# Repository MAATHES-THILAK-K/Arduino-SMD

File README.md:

# Arduino-SMD

GrabCAD Link: [https://grabcad.com/library/arduino-smd-1](https://grabcad.com/library/arduino-smd-1)

This project is a compact, stylish, Arduino-compatible development board based on the **ATmega328P-AU** (TQFP). It includes several integrated peripherals making it ideal for wearable or IoT projects.

---

## 📦 Components

| Component                              | Description                               |
| -------------------------------------- | ----------------------------------------- |
| **ATmega328P-AU**                      | 8-bit microcontroller (TQFP)              |
| **AMS1117-3.3V LDO**                   | 5V to 3.3V regulator for APDS9960 & HC-05 |
| **TLV76750**                           | 12V to 5V LDO                             |
| **WS2812B**                            | RGB LED (Smart addressable)               |
| **APDS-9960**                          | Gesture sensor (I2C)                      |
| **HC-05**                              | Bluetooth module                          |
| **Tactile Switch**                     | User input                                |
| **Active Buzzer**                      | Sound feedback                            |
| **USB-C (Power-only)**                 | 5V input only (no data lines)             |
| **12V Barrel Jack**                    | Additional power input                    |
| **ICSP Header (2x3)**                  | For firmware flashing                     |
| **GPIO Headers**                       | Female headers for D0-D13, A0-A5          |
| **Various SMD Resistors & Capacitors** | For pull-ups, bypassing, filtering        |

---

## ⚠️ Warning

> **The DRC (Design Rule Check) in KiCad was not fully resolved during initial layout. There may be trace width, clearance, or connectivity issues. Please verify the layout manually or run a complete DRC pass before fabrication.**

---

## 📁 Folder Info

* **Gerber/** → Ready-to-export Gerber files for fabrication
* **KiCad\_Project/** → All source files for the schematic & layout
* **images/** → (Optional) Screenshots, 3D renders of the board
* **LICENSE** → MIT License for reuse
* **.gitignore** → Standard for KiCad projects

---

## 🛠️ To-Do

* [ ] Fix all DRC errors
* [ ] Add 3D renders
* [ ] Test hardware once fabricated

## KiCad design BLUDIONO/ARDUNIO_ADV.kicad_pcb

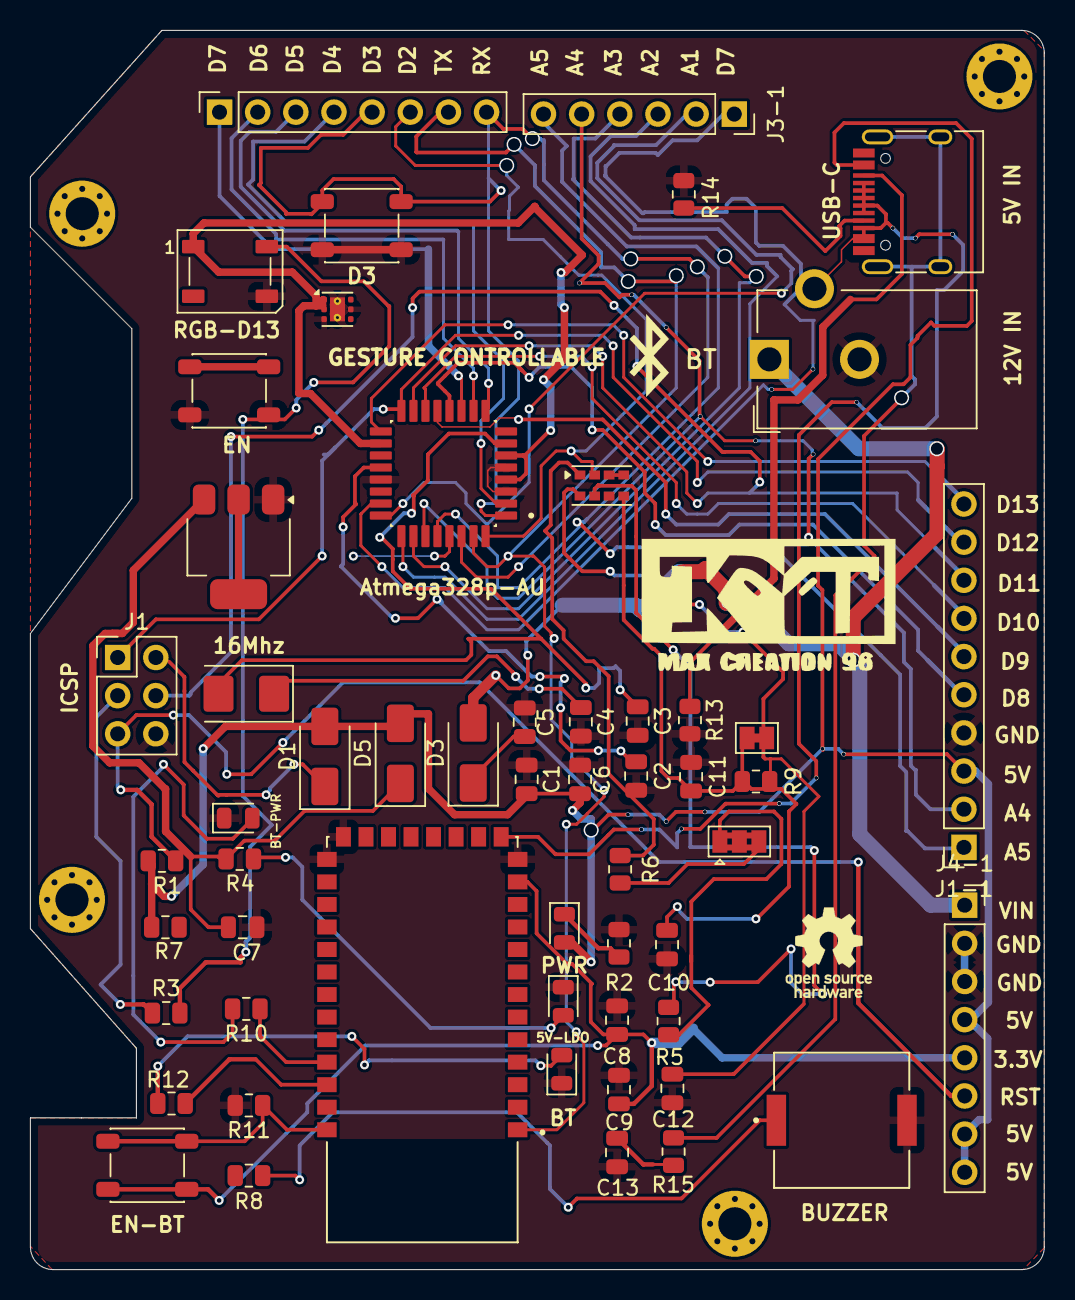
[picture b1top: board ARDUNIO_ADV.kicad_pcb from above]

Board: 2 copper layers, 67.5 x 82.5 mm, 59 parts (0 on the bottom side), 51 nets.

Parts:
5V-LDO: LED; LED_0805_2012Metric
12V IN: Barrel_Jack; BarrelJack_CUI_PJ-102AH_Horizontal
16Mhz: Crystal; Crystal_SMD_5032-2Pin_5.0x3.2mm
BT: LED; LED_0805_2012Metric
BT-PWR: LED; LED_0805_2012Metric
BZ1: Buzzer; SPKR_PKMCS0909E4000-R1
C1, C2, C13: 100nf; C_0805_2012Metric
C3, C4: 22pf; C_0805_2012Metric
C5: 1uf; C_0805_2012Metric
C6: 2.2uf; C_0805_2012Metric
C7, C8: 10uf; C_0805_2012Metric
C9: 0.1uf; C_0805_2012Metric
C10: 1.0uf; C_0805_2012Metric
C11: 100uf; C_0805_2012Metric
C12: 1.0fu; C_0805_2012Metric
D1, D3#2, D5: SS14; D_SMA
D3: SW_DPST_x2; SW_SPST_PTS647_Sx50
EN: SW_DPST_x2; SW_SPST_PTS647_Sx50
EN-BT: SW_DPST_x2; SW_SPST_PTS647_Sx50
H1, H2, H3, H4: MountingHole; MountingHole_2.2mm_M2_Pad_Via
J1: ICSP; PinHeader_2x03_P2.54mm_Vertical
J1-1: Conn_01x10_Pin; PinSocket_1x10_P2.54mm_Vertical
J2-1, J4-1: Conn_01x08_Pin; PinSocket_1x08_P2.54mm_Vertical
J3-1: Conn_01x06_Pin; PinSocket_1x06_P2.54mm_Vertical
JP1: SolderJumper_3_Bridged123; SolderJumper-3_P1.3mm_Bridged2Bar123_Pad1.0x1.5mm
JP2: SolderJumper_2_Bridged; SolderJumper-2_P1.3mm_Bridged_Pad1.0x1.5mm
PWR: LED; LED_0805_2012Metric
R1, R7, R11: 10k; R_0805_2012Metric
R2, R12: 1k; R_0805_2012Metric
R3: 330; R_0805_2012Metric
R4: 2.2k; R_0805_2012Metric
R5, R6: 4.7k; R_0805_2012Metric
R8: 100; R_0805_2012Metric
R9: DNP; R_0805_2012Metric
R10: 2k; R_0805_2012Metric
R13, R14: 5.1k; R_0805_2012Metric
R15: 1M; R_0805_2012Metric
RGB-D13: WS2812B; LED_WS2812B_PLCC4_5.0x5.0mm_P3.2mm
U1: ATMEGA328P-AU; QFP80P900X900X120-32N
U2: TLV76750DRVx; WSON-6-1EP_2x2mm_P0.65mm_EP1x1.6mm_ThermalVias
U3: AMS1117-3.3; SOT-223-3_TabPin2
U4: APDS-9960; Avago_APDS-9960
U5: HC-05; XCVR_HC-05
USB-C: USB_C_Receptacle_PowerOnly_6P; USB_C_Receptacle_HRO_TYPE-C-31-M-12

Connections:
3.3v: C8.1, C9.1, EN-BT.2 (B), J4-1.5, U3.2 (VO), U5.12 (3.3_VCC)
5V: C1.2, C6.1, D1.2 (A), D5.2 (A), J1-1.3, J4-1.4, J4-1.7, J4-1.8, PWR.2 (A), R1.2, R7.1, RGB-D13.1 (VDD), U1.4 (VCC), U1.6 (VCC__1), U1.18 (AVCC), U2.1 (OUT), U2.2 (SNS), USB-C.A9 (VBUS), USB-C.B9 (VBUS)
A0: J3-1.1, U1.23 (PC0)
A1: J3-1.2, U1.24 (PC1)
A2: J3-1.3, U1.25 (PC2)
A3: J3-1.4, U1.26 (PC3)
A4: J1-1.2, J3-1.5, U1.27 (PC4)
A5: J1-1.1, J3-1.6, U1.28 (PC5)
D2: J2-1.6, R7.2, U1.32 (PD2), U4.2 (INT)
D3: D3.1 (A), J2-1.5, U1.1 (PD3)
D4: J2-1.4, U1.2 (PD4)
D5: J2-1.3, U1.9 (PD5)
D6: J2-1.2, R8.1, U1.10 (PD6)
D7: J2-1.1, U1.11 (PD7)
D8: J1-1.5, U1.12 (PB0)
D9: J1-1.6, U1.13 (PB1)
D10: J1-1.7, U1.14 (PB2)
D11: J1.4, J1-1.8, U1.15 (PB3)
D12: J1.1, J1-1.9, U1.16 (PB4)
D13: J1.3, J1-1.10, R3.1, U1.17 (PB5)
GND: 5V-LDO.1 (K), 12V IN.2, BT.1 (K), BT-PWR.1 (K), BZ1.2 (-), C1.1, C2.2, C3.2, C4.2, C5.2, C6.2, C7.2, C8.2, C9.2, C10.1, C11.2, C12.2, C13.2, D3.2 (B), EN.2 (B), J1.6, J1-1.4, J4-1.2, J4-1.3, R2.1, R11.2, R13.2, R14.2, RGB-D13.3 (VSS), U1.3 (GND), U1.5 (GND__1), U1.21 (GND__2), U2.3 (GND), U2.5 (GND), U2.7 (PAD), U3.1 (GND), U4.6 (GND), U5.13 (GND), U5.21 (GND), U5.22 (GND), USB-C.A12 (GND), USB-C.B12 (GND)
unnamed: BZ1.1 (+), R8.2
unnamed: C13.1, R15.2
unnamed: D1.1 (K), J1.2
unnamed: PWR.1 (K), R2.2
unnamed: C5.1, D3#2.1 (K), U2.4 (EN), U2.6 (IN)
unnamed: R3.2, RGB-D13.4 (DIN)
unnamed: C7.1, D5.1 (K), R4.1, U3.3 (VI)
unnamed: 5V-LDO.2 (A), R4.2
unnamed: BT-PWR.2 (A), R10.2
unnamed: BT.2 (A), R12.1
unnamed: R14.1, USB-C.A5 (CC1)
unnamed: R13.1, USB-C.B5 (CC2)
unnamed: R15.1, USB-C.S1 (SHIELD)
unnamed: JP1.1 (A), R5.1
unnamed: JP1.3 (B), R6.1
unnamed: C12.1, JP2.2 (B), R9.1, U4.8 (VDD)
unnamed: EN-BT.1 (A), R11.1, U5.34 (PIO[11])
unnamed: C2.1, U1.20 (AREF)
unnamed: U4.3 (LDR), U4.4 (LED_K)
unnamed: R10.1, U5.31 (PIO[8])
PB6: 16Mhz.2, C3.1, U1.7 (PB6)
PB7: 16Mhz.1, C4.1, U1.8 (PB7)
RST: EN.1 (A), J1.5, J4-1.6, R1.1, U1.29 (PC6/~RESET)
RX: J2-1.8, U1.30 (PD0), U5.2 (UART-RX)
SCL: R5.2, U4.7 (SCL)
SDA: R6.2, U4.1 (SDA)
STATE: R12.2, U5.32 (PIO[9])
TX: J2-1.7, U1.31 (PD1), U5.1 (UART-TX)
Vin: 12V IN.1, D3#2.2 (A), J4-1.1
Vl: C10.2, C11.1, JP2.1 (A), R9.2, U4.5 (LED_A)

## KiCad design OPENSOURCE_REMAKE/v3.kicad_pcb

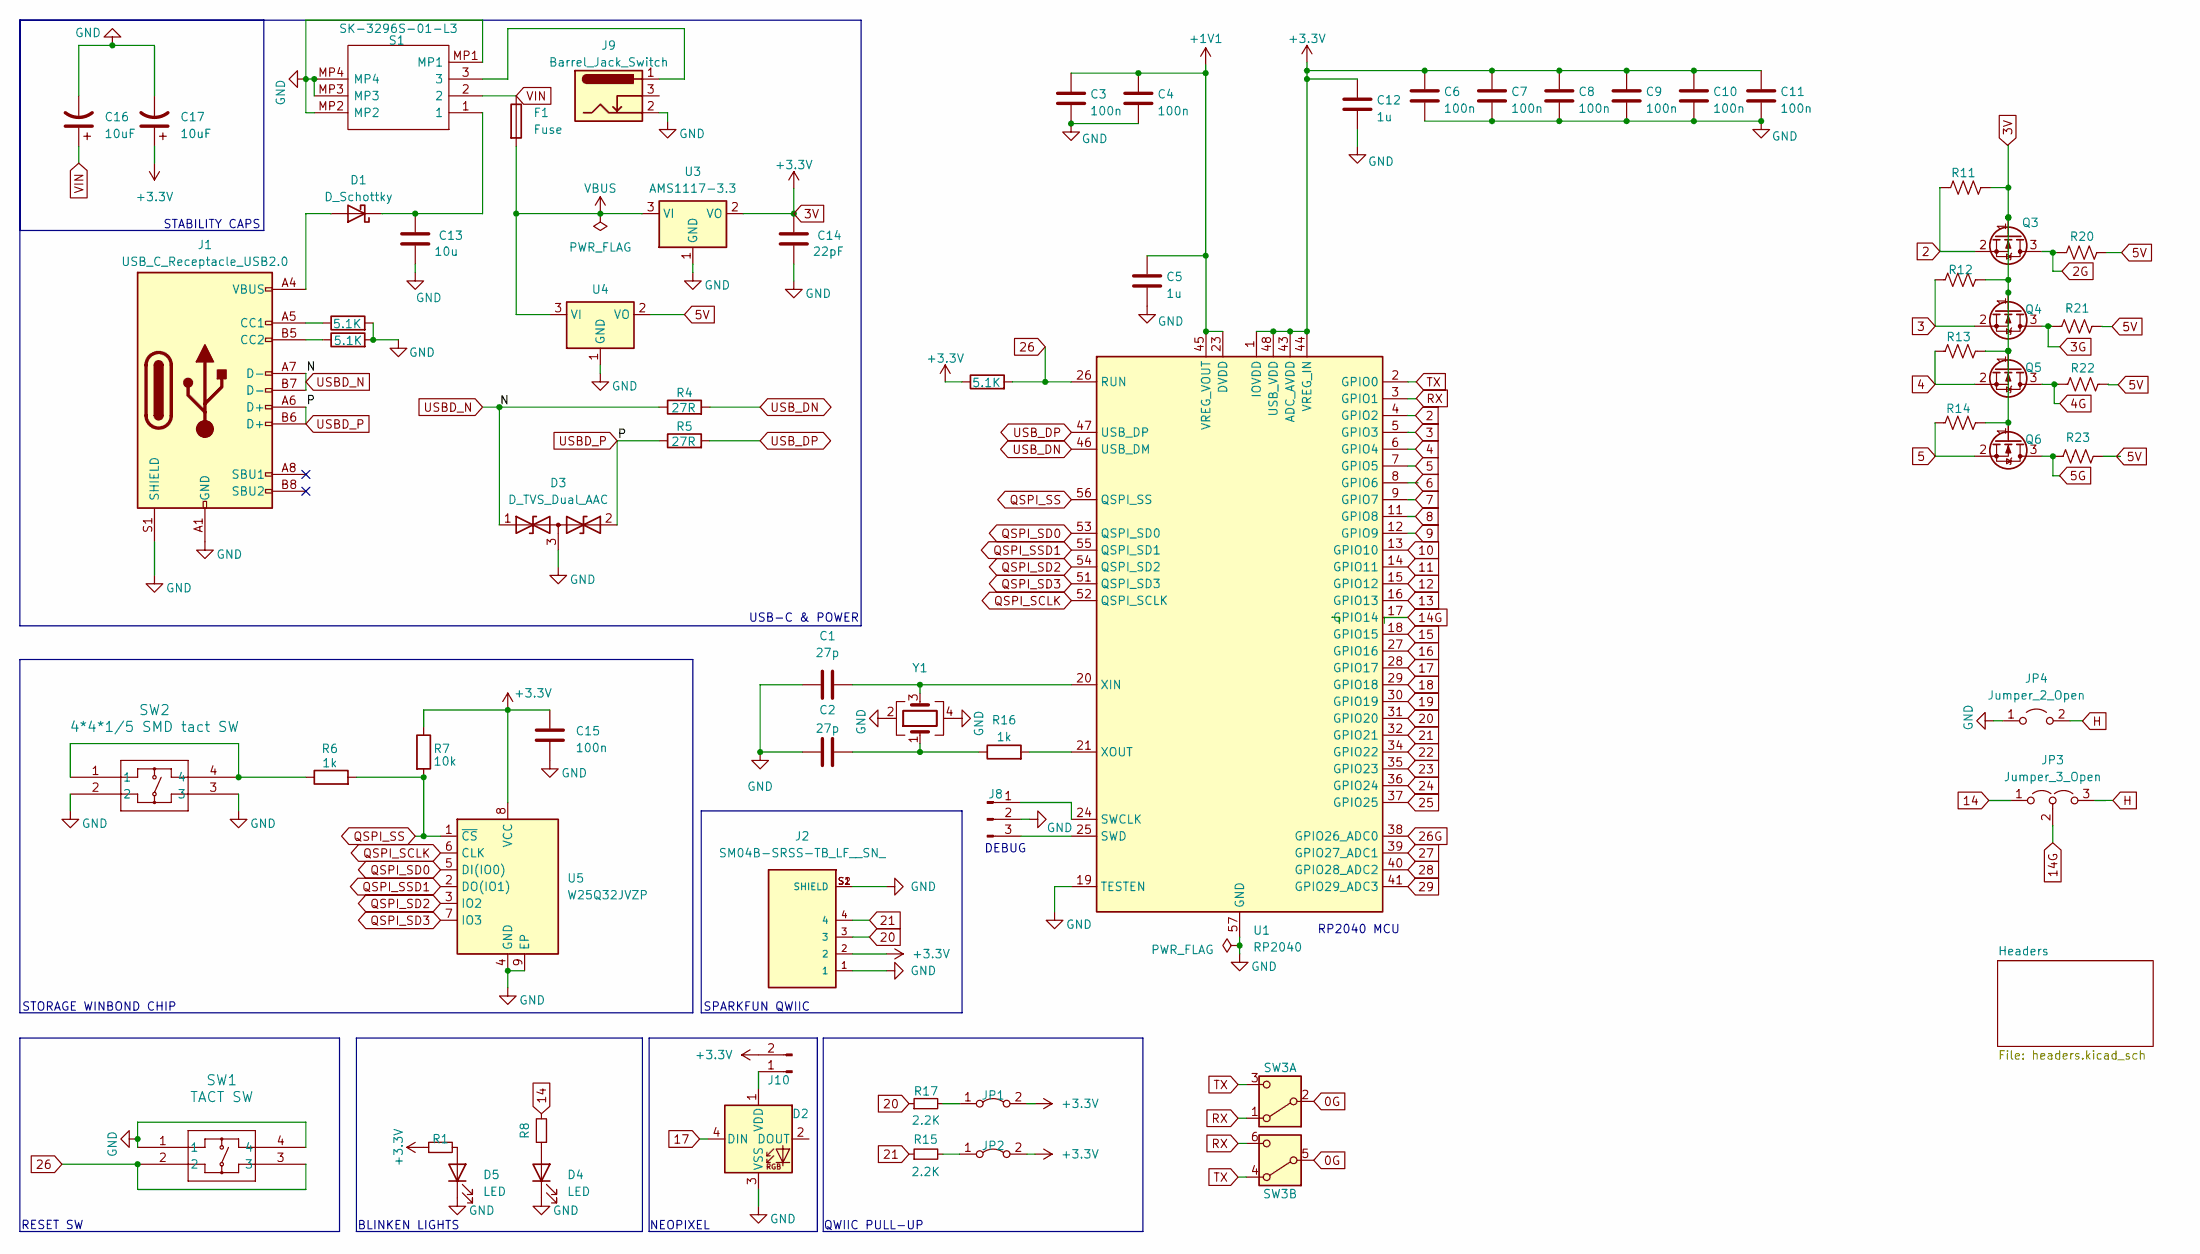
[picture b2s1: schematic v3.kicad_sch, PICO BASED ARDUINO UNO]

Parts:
C1, C2: 27p; C_0402_1005Metric_Pad0.74x0.62mm_HandSolder
C3, C4, C6, C7, C8, C9, C10, C11, C15: 100n; C_0402_1005Metric_Pad0.74x0.62mm_HandSolder
C5, C12: 1u; C_0402_1005Metric_Pad0.74x0.62mm_HandSolder
C13: 10u; C_0402_1005Metric_Pad0.74x0.62mm_HandSolder
C14: 22pF; C_0402_1005Metric_Pad0.74x0.62mm_HandSolder
C16, C17: 10uF; CP_Elec_4x5.4; LCSC C4747971
D1: D_Schottky; D_SOD-128
D2: WS2812B; LED_WS2812B_PLCC4_5.0x5.0mm_P3.2mm
D3: D_TVS_Dual_AAC; SOT-23
D4, D5: LED; LED_0805_2012Metric_Pad1.15x1.40mm_HandSolder
F1: Fuse; Fuse_1206_3216Metric_Pad1.42x1.75mm_HandSolder
J1: USB_C_Receptacle_USB2.0; USB_C_Receptacle_G-Switch_GT-USB-7010ASV
J2: SM04B-SRSS-TB_LF__SN_; JST_SM04B-SRSS-TB_LF__SN_
J8: Conn_01x03_Pin; PinSocket_1x03_P2.54mm_Vertical
J9: Barrel_Jack_Switch; BarrelJack_Horizontal
J10: Conn_01x02_Pin; PinHeader_1x02_P2.54mm_Vertical
JP1, JP2: Jumper_2_Bridged; SolderJumper-2_P1.3mm_Open_RoundedPad1.0x1.5mm
JP3: Jumper_3_Open; SolderJumper-3_P1.3mm_Open_Pad1.0x1.5mm
JP4: Jumper_2_Open; SolderJumper-2_P1.3mm_Open_RoundedPad1.0x1.5mm
Q3, Q4, Q5, Q6: BSS138; SOT-23
R1, R8: 220; R_0402_1005Metric_Pad0.72x0.64mm_HandSolder
R2, R3, R33: 5.1K; R_0402_1005Metric_Pad0.72x0.64mm_HandSolder
R4, R5: 27R; R_0402_1005Metric_Pad0.72x0.64mm_HandSolder
R6, R16: 1k; R_0402_1005Metric_Pad0.72x0.64mm_HandSolder
R7: 10k; R_0402_1005Metric_Pad0.72x0.64mm_HandSolder
R11, R12, R13, R14, R20, R21, R22, R23: 10K; R_0402_1005Metric_Pad0.72x0.64mm_HandSolder
R15, R17: 2.2K; R_0402_1005Metric_Pad0.72x0.64mm_HandSolder
S1: SK-3296S-01-L3; SK3296S01L3; Manufacturer_Part_Number SK-3296S-01-L3
SW1: TACT SW; SW_SPST_TL3342
SW2: 4*4*1/5 SMD tact SW; SW_SPST_TL3342
SW3: SW_DPDT_x2; SW_CL-SB-22A-02T; MFG Part No C2904912
U1: RP2040; QFN-56-1EP_7x7mm_P0.4mm_EP3.2x3.2mm
U3: AMS1117-3.3; SOT-223-3_TabPin2
U4: AMS1117-5.0; SOT-223-3_TabPin2
U5: W25Q32JVZP; WSON-8-1EP_6x5mm_P1.27mm_EP3.4x4.3mm
Y1: \YSX321SL 12 Mhz; Crystal_SMD_3225-4Pin_3.2x2.5mm

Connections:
0G: SW3.2 (B), SW3.5 (B)
2: Q3.2 (S), R11.1, U1.4 (GPIO2)
2G: Q3.3 (D), R20.1
3: Q4.2 (S), R12.1, U1.5 (GPIO3)
3G: Q4.3 (D), R21.1
3V: C6.1, C7.1, C8.1, C9.1, C10.1, C11.1, C12.1, C14.1, C15.1, C17.1, J2.2, J10.2, JP1.2 (B), JP2.2 (B), Q3.1 (G), Q4.1 (G), Q5.1 (G), Q6.1 (G), R1.1, R7.1, R11.2, R12.2, R13.2, R14.2, R33.1, U1.1 (IOVDD), U1.10 (IOVDD), U1.22 (IOVDD), U1.33 (IOVDD), U1.42 (IOVDD), U1.43 (ADC_AVDD), U1.44 (VREG_IN), U1.48 (USB_VDD), U1.49 (IOVDD), U3.2 (VO), U5.8 (VCC); also elsewhere on the board
4: Q5.2 (S), R13.1, U1.6 (GPIO4)
4G: Q5.3 (D), R22.1
5: Q6.2 (S), R14.1, U1.7 (GPIO5)
5G: Q6.3 (D), R23.1
5V: R20.2, R21.2, R22.2, R23.2, U4.2 (VO); also elsewhere on the board
6: U1.8 (GPIO6)
7: U1.9 (GPIO7)
8: U1.11 (GPIO8)
9: U1.12 (GPIO9)
10: U1.13 (GPIO10)
11: U1.14 (GPIO11)
12: U1.15 (GPIO12)
13: U1.16 (GPIO13)
14: JP3.1 (A), R8.2
14G: JP3.2 (C), U1.17 (GPIO14)
15: U1.18 (GPIO15)
16: U1.27 (GPIO16)
17: D2.4 (DIN), U1.28 (GPIO17); also elsewhere on the board
18: U1.29 (GPIO18)
19: U1.30 (GPIO19)
20: J2.3, R17.1, U1.31 (GPIO20); also elsewhere on the board
21: J2.4, R15.1, U1.32 (GPIO21); also elsewhere on the board
22: U1.34 (GPIO22)
23: U1.35 (GPIO23)
24: U1.36 (GPIO24); also elsewhere on the board
25: U1.37 (GPIO25); also elsewhere on the board
26: R33.2, SW1.2, SW1.3, U1.26 (RUN); also elsewhere on the board
26G: U1.38 (GPIO26_ADC0)
27: U1.39 (GPIO27_ADC1)
28: U1.40 (GPIO28_ADC2)
29: U1.41 (GPIO29_ADC3)
+1V1: C3.1, C4.1, C5.1, U1.23 (DVDD), U1.45 (VREG_VOUT), U1.50 (DVDD)
GND: C1.1, C2.1, C3.2, C4.2, C5.2, C6.2, C7.2, C8.2, C9.2, C10.2, C11.2, C12.2, C13.2, C14.2, C15.2, C16.2, C17.2, D2.3 (VSS), D3.3 (common), D4.1 (K), D5.1 (K), J1.A1 (GND), J1.A12 (GND), J1.B1 (GND), J1.B12 (GND), J1.S1 (SHIELD), J2.1, J2.S1 (SHIELD), J2.S2 (SHIELD), J8.2, J9.2, JP4.1 (A), R2.2, R3.2, S1.MP1, S1.MP2, S1.MP3, S1.MP4, SW1.1, SW1.4, SW2.2, SW2.3, U1.19 (TESTEN), U1.57 (GND), U3.1 (GND), U4.1 (GND), U5.4 (GND), U5.9 (EP), Y1.2, Y1.4; also elsewhere on the board
H: JP3.3 (B), JP4.2 (B)
unnamed: C2.2, R16.1, Y1.1
unnamed: D1.2 (A), J1.A4 (VBUS), J1.A9 (VBUS), J1.B4 (VBUS), J1.B9 (VBUS)
unnamed: C13.1, D1.1 (K), S1.1
unnamed: D2.1 (VDD), J10.1
unnamed: D4.2 (A), R8.1
unnamed: D5.2 (A), R1.2
unnamed: J1.A5 (CC1), R2.1
unnamed: J1.B5 (CC2), R3.1
unnamed: J8.1, U1.24 (SWCLK)
unnamed: J8.3, U1.25 (SWD)
unnamed: J9.1, S1.3
unnamed: JP1.1 (A), R17.2
unnamed: JP2.1 (A), R15.2
unnamed: R6.1, SW2.1, SW2.4
unnamed: C1.2, U1.20 (XIN), Y1.3
unnamed: R16.2, U1.21 (XOUT)
QSPI_SCLK: U1.52 (QSPI_SCLK), U5.6 (CLK)
QSPI_SD0: U1.53 (QSPI_SD0), U5.5 (DI(IO0))
QSPI_SD2: U1.54 (QSPI_SD2), U5.3 (IO2)
QSPI_SD3: U1.51 (QSPI_SD3), U5.7 (IO3)
QSPI_SS: R6.2, R7.2, U1.56 (QSPI_SS), U5.1 (~CS)
QSPI_SSD1: U1.55 (QSPI_SD1), U5.2 (DO(IO1))
RX: SW3.1 (A), SW3.6 (C), U1.3 (GPIO1)
TX: SW3.3 (C), SW3.4 (A), U1.2 (GPIO0)
USBD_N: D3.1 (A1), J1.A7 (D-), J1.B7 (D-), R4.1
USBD_P: D3.2 (A2), J1.A6 (D+), J1.B6 (D+), R5.1
USB_DN: R4.2, U1.46 (USB_DM)
USB_DP: R5.2, U1.47 (USB_DP)
VBUS: F1.2, U3.3 (VI), U4.3 (VI)
VIN: C16.1, F1.1, S1.2; also elsewhere on the board

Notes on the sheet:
NEOPIXEL
RP2040 MCU
SPARKFUN QWIIC
STABILITY CAPS
RESET SW
DEBUG
STORAGE WINBOND CHIP
QWIIC PULL-UP
BLINKEN LIGHTS
USB-C & POWER

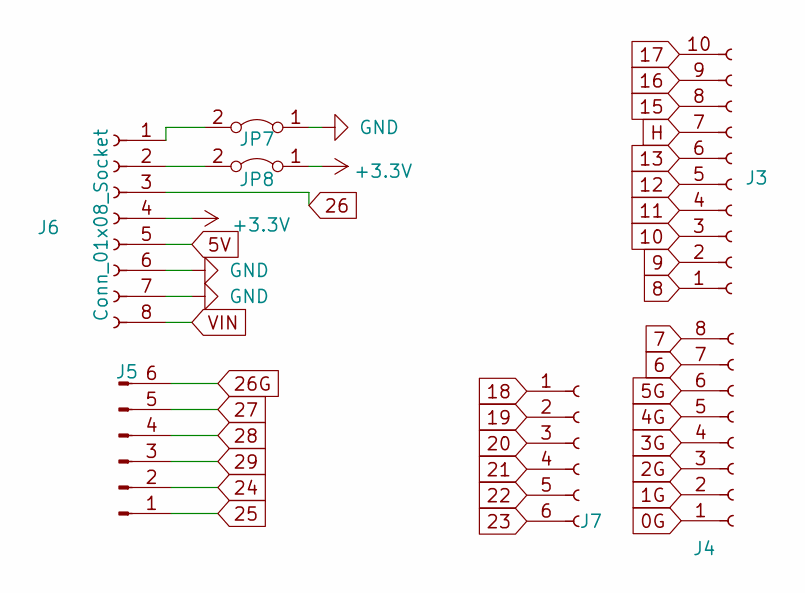
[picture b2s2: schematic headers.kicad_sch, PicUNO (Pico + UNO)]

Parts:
J3: Conn_01x10_Socket; PinSocket_1x10_P2.54mm_Vertical
J4, J6: Conn_01x08_Socket; PinSocket_1x08_P2.54mm_Vertical
J5: Conn_01x06_Pin; PinSocket_1x06_P2.54mm_Vertical
J7: Conn_01x06_Socket; PinSocket_1x06_P2.54mm_Vertical
JP7, JP8: Jumper_2_Bridged; SolderJumper-2_P1.3mm_Open_RoundedPad1.0x1.5mm

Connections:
3V: J6.4, JP8.1 (A); also elsewhere on the board
5V: J6.5; also elsewhere on the board
17: J3.10; also elsewhere on the board
20: J7.3; also elsewhere on the board
21: J7.4; also elsewhere on the board
24: J5.2; also elsewhere on the board
25: J5.1; also elsewhere on the board
26: J6.3; also elsewhere on the board
GND: J6.6, J6.7, JP7.1 (A); also elsewhere on the board
unnamed 69: J6.1, JP7.2 (B); also elsewhere on the board
unnamed 70: J6.2, JP8.2 (B); also elsewhere on the board
VIN: J6.8; also elsewhere on the board

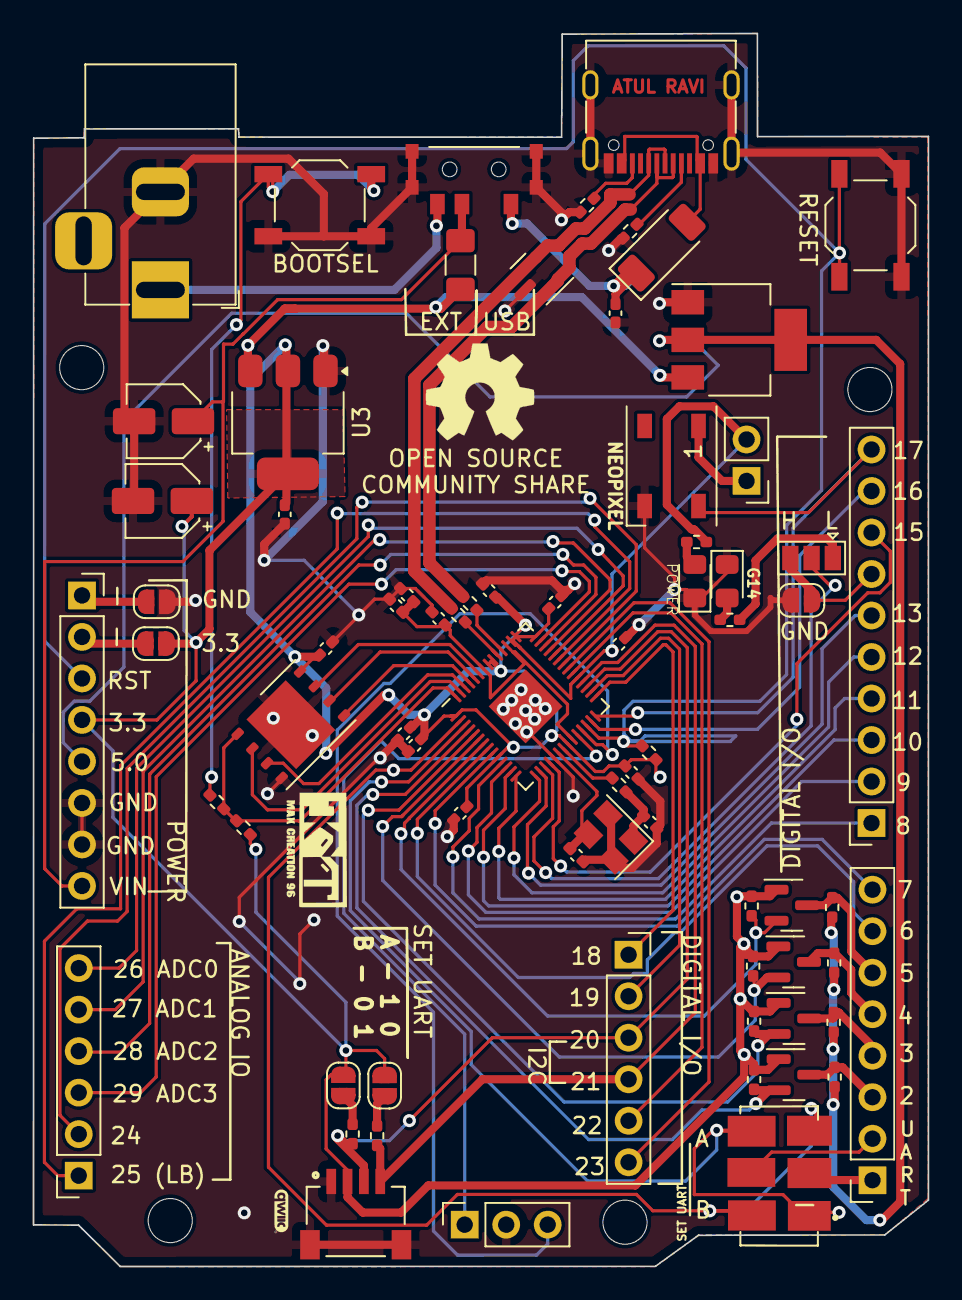
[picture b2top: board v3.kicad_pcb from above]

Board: 2 copper layers, 54.8 x 75.5 mm, 75 parts (0 on the bottom side), 54 nets.

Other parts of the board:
JP5, JP6: Jumper_2_Bridged; SolderJumper-2_P1.3mm_Open_RoundedPad1.0x1.5mm
REF1**, REF2**, REF3**: MountingHole_2.7mm_M2.5_ISO14580

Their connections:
3V: JP5.1 (A); also elsewhere on the board
GND: JP6.1 (A); also elsewhere on the board
unnamed 69: JP6.2 (B); also elsewhere on the board
unnamed 70: JP5.2 (B); also elsewhere on the board

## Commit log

2025-06-26 3D View of the PCB is uploaded as Image
2025-06-26 Added bare minimum Arduino-board configuration
2025-06-26 Kicad files are uploaded
2025-06-26 Drill files are Uploaded !!
2025-06-26 Gerber files are uploaded for Fabrication
    Read the Readme.md before using the Gerber files !!
2025-06-26 .step file is added for 3D Model
2025-08-07 Pheripherals shematics added
2026-01-29 Create TEMP
2026-01-31 Create 3D MODEL
